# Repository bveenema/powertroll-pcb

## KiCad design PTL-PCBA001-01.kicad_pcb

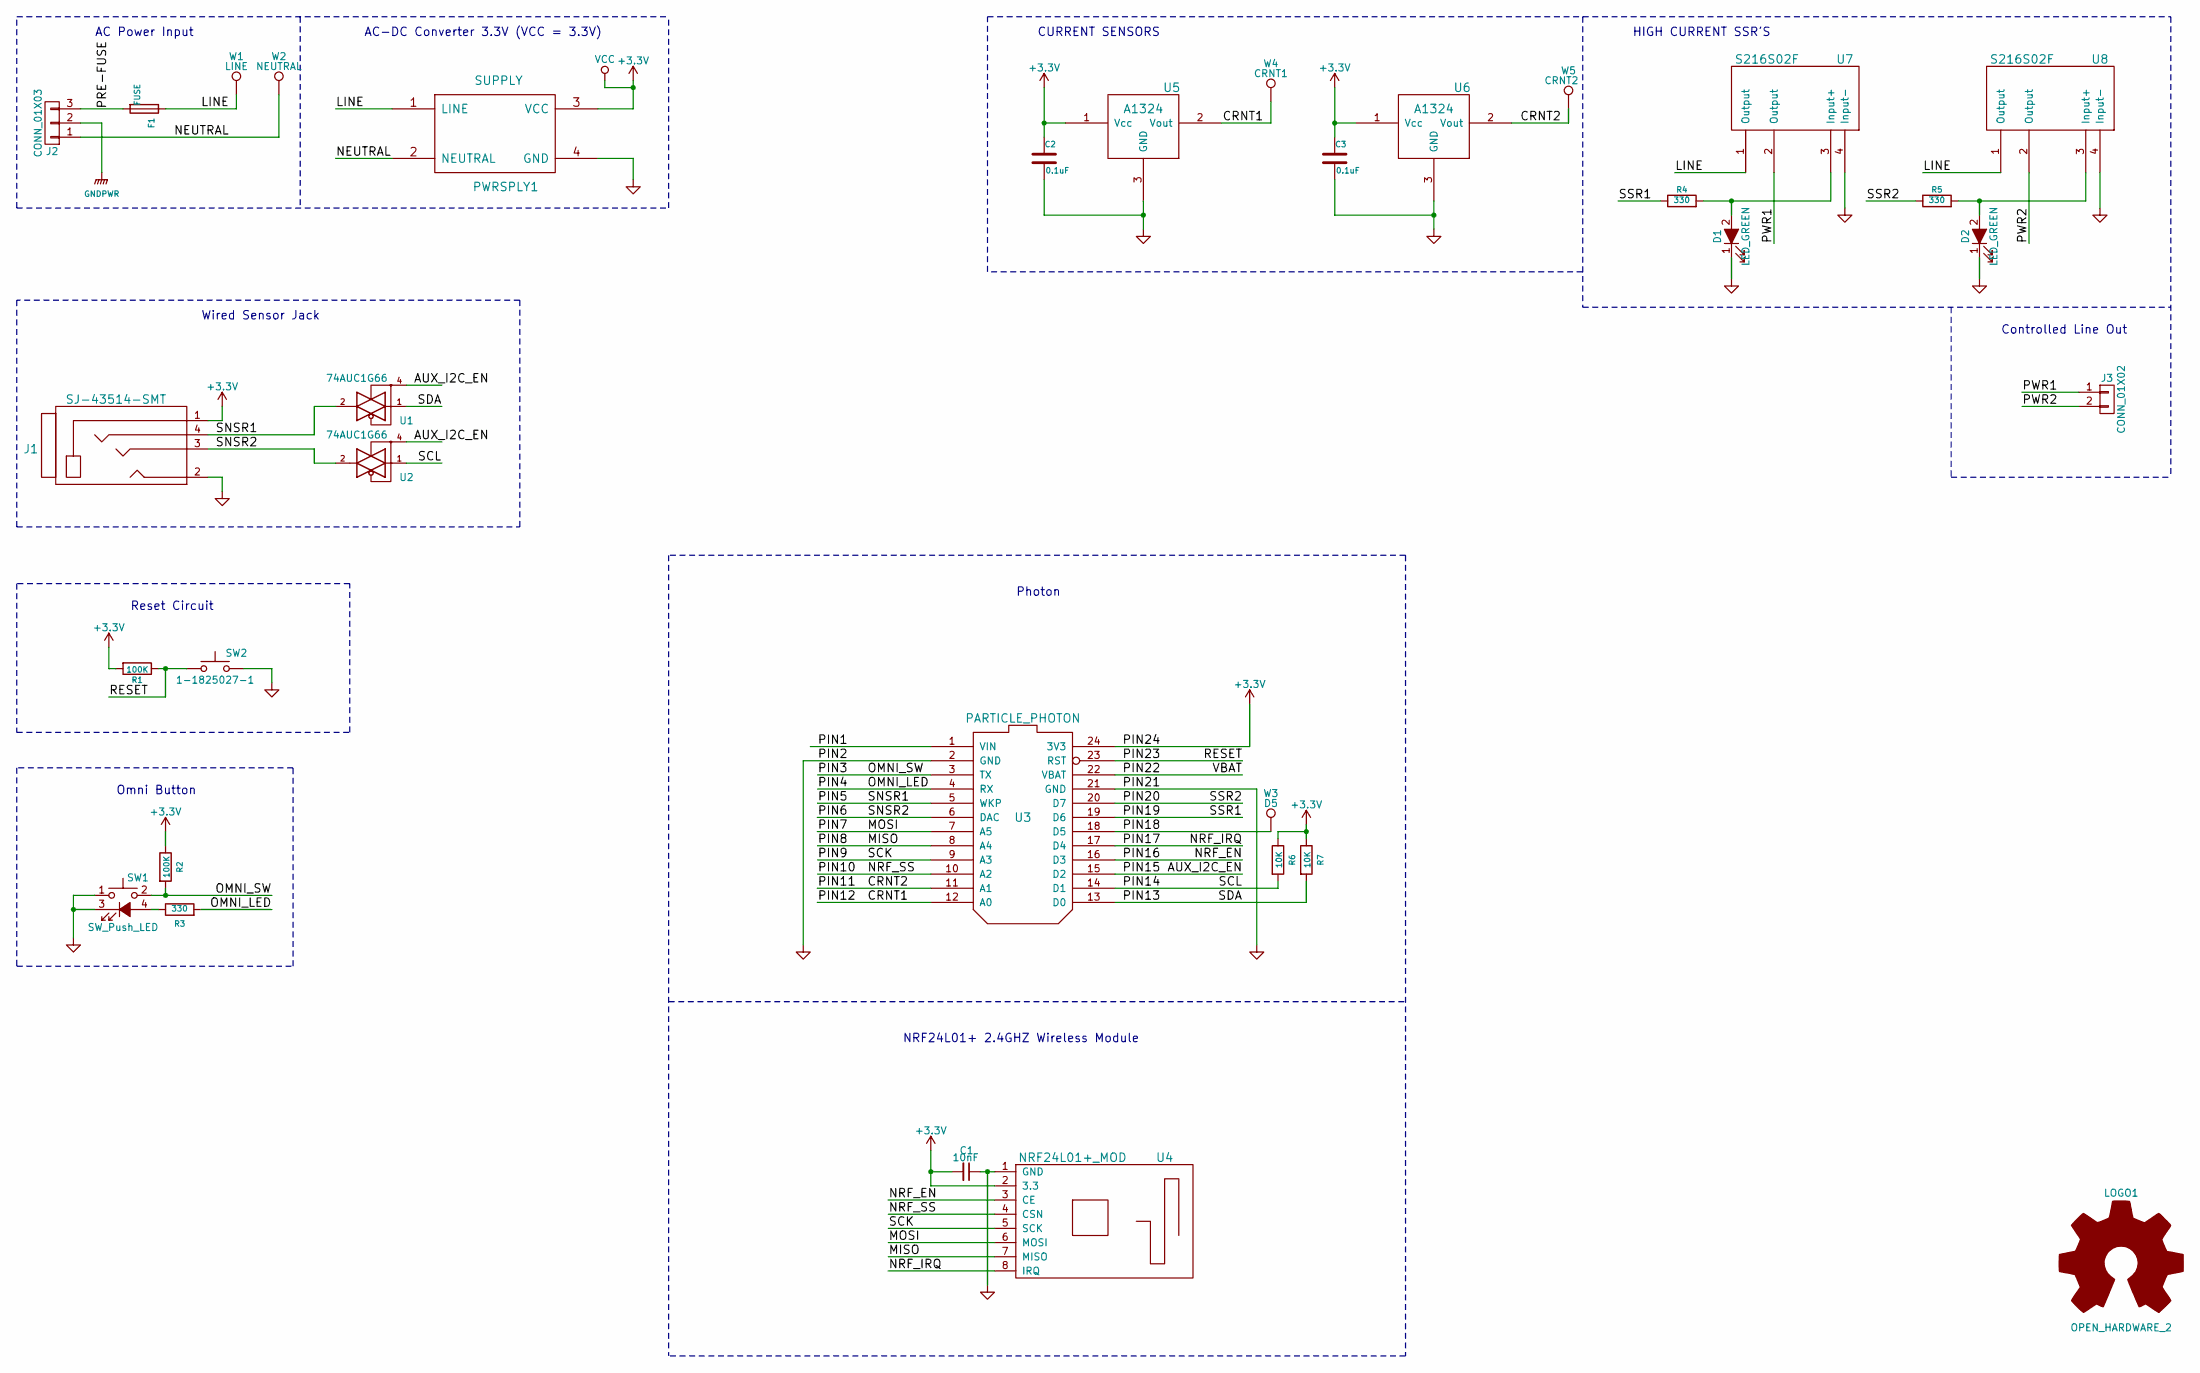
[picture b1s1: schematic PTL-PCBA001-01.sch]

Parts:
C1: 10nF; C_0805; Part Number CL21B103KBANNNC
C2, C3: 0.1uF; C_0805_HandSoldering
D1, D2: LED_GREEN; LED_0805
F1: FUSE; Fuseholder5x20_horiz_open_inline_Type-I
J1: SJ-43514-SMT
J2: CONN_01X03; Molex_UltraFit-1722861103_3x3.50mm_Straight
J3: CONN_01X02; Molex_UltraFit-1722861102_2x3.50mm_Straight
LOGO1: OPEN_HARDWARE_2; OSHW-Symbol_6.7x6mm_SilkScreen
PWRSPLY1: SUPPLY; PowerSupply
R1, R2: 100K; R_0805_HandSoldering
R3, R4, R5: 330; R_0805_HandSoldering
R6, R7: 10K; R_0805_HandSoldering
SW1: SW_Push_LED; JST_PH_B4B-PH-K_04x2.00mm_Straight
SW2: 1-1825027-1; SW_Tactile_SPST_Angled
U1, U2: 74AUC1G66; SOT-23-5
U3: PARTICLE_PHOTON; photon
U4: NRF24L01+_MOD; NRF24L01
U5, U6: A1324; SOT-23
U7, U8: S216S02F; S216S02
W1: LINE; Measurement_Point_Round-TH_Small
W2: NEUTRAL; Measurement_Point_Round-TH_Small
W3: D5; Measurement_Point_Round-TH_Small
W4: CRNT1; Measurement_Point_Round-SMD-Pad_Small
W5: CRNT2; Measurement_Point_Round-SMD-Pad_Small

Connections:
+3V3: C1.2, C2.1, C3.1, J1.1, PWRSPLY1.3 (VCC), R1.2, R2.1, R6.1, R7.1, U1.5 (VCC), U2.5 (VCC), U3.24 (3V3), U4.2 (3.3), U5.1 (Vcc), U6.1 (Vcc)
/AUX_I2C_EN: U1.4, U2.4, U3.15 (D2)
/CRNT1: U3.12 (A0), U5.2 (Vout), W4.1
/CRNT2: U3.11 (A1), U6.2 (Vout), W5.1
/LINE: F1.1, PWRSPLY1.1 (LINE), U7.1 (Output), U8.1 (Output), W1.1
/MISO: U3.8 (A4), U4.7 (MISO)
/MOSI: U3.7 (A5), U4.6 (MOSI)
/NEUTRAL: J2.1, PWRSPLY1.2 (NEUTRAL), W2.1
/NRF_EN: U3.16 (D3), U4.3 (CE)
/NRF_IRQ: U3.17 (D4), U4.8 (IRQ)
/NRF_SS: U3.10 (A2), U4.4 (CSN)
/OMNI_LED: R3.2, U3.4 (RX)
/OMNI_SW: R2.2, SW1.2, U3.3 (TX)
/PIN1: U3.1 (VIN)
/PIN5: J1.4, U1.2, U3.5 (WKP)
/PIN6: J1.3, U2.2, U3.6 (DAC)
/PIN9: U3.9 (A3), U4.5 (SCK)
/PIN13: R7.2, U1.1, U3.13 (D0)
/PIN14: R6.2, U2.1, U3.14 (D1)
/PIN18: U3.18 (D5), W3.1
/PIN19: R4.1, U3.19 (D6)
/PIN20: R5.1, U3.20 (D7)
/PIN22: U3.22 (VBAT)
/PIN23: R1.1, SW2.1, U3.23 (RST)
/PRE-FUSE: F1.2, J2.3
/PWR1: J3.1, U7.2 (Output)
/PWR2: J3.2, U8.2 (Output)
GND: C1.1, C2.2, C3.2, D1.1 (K), D2.1 (K), J1.2, PWRSPLY1.4 (GND), SW1.1, SW1.3 (K), SW2.2, U1.3 (GND), U2.3 (GND), U3.2 (GND), U3.21 (GND), U4.1 (GND), U5.3 (GND), U6.3 (GND), U7.4 (Input-), U8.4 (Input-)
GNDPWR: J2.2
unnamed: D1.2 (A), R4.2, U7.3 (Input+)
unnamed: D2.2 (A), R5.2, U8.3 (Input+)
unnamed: R3.1, SW1.4 (A)

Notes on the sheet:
HIGH CURRENT SSR'S
CURRENT SENSORS
AC-DC Converter 3.3V (VCC = 3.3V)
AC Power Input
Wired Sensor Jack
Controlled Line Out
Reset Circuit
Photon
NRF24L01+ 2.4GHZ Wireless Module
Omni Button

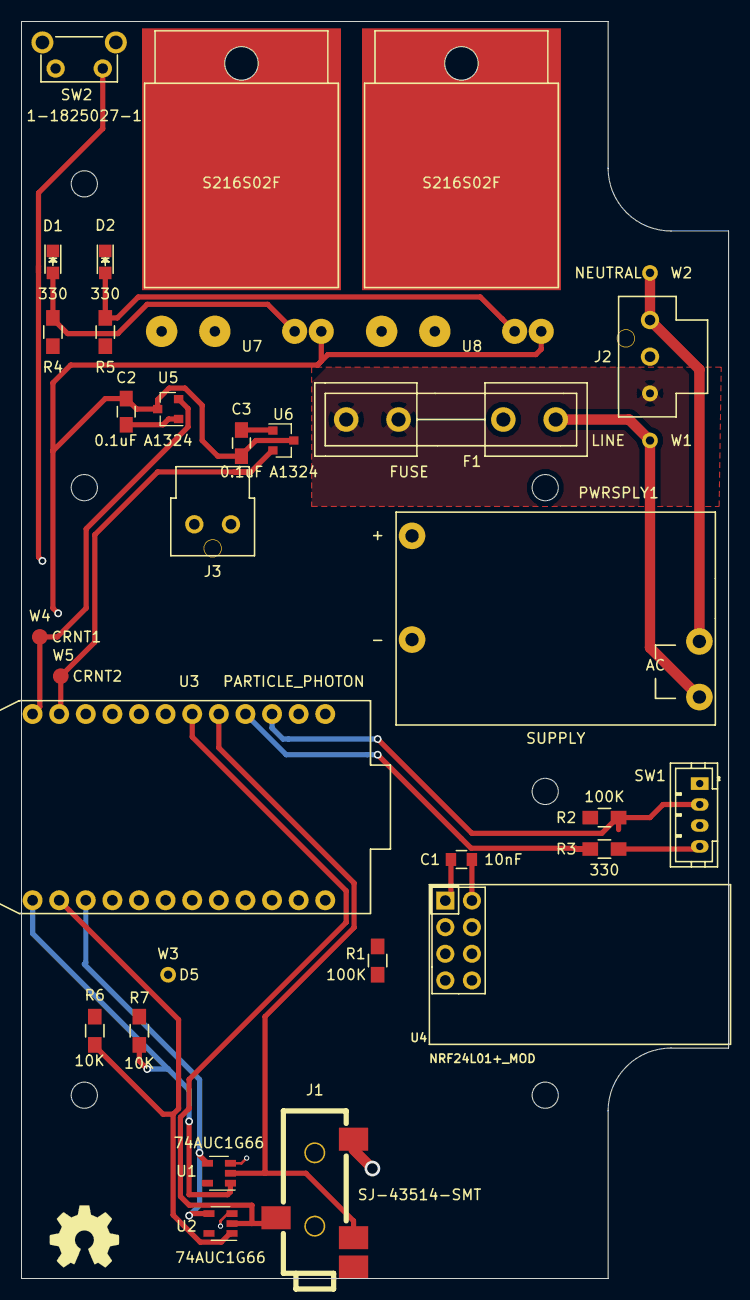
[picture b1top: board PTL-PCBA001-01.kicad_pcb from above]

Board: 2 copper layers, 67.5 x 120.0 mm, 33 parts (0 on the bottom side), 29 nets.

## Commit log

2016-12-19 Included files from previous version
2016-12-20 Completed Schematic
2016-12-21 Restore after Gdrive ruined everything
2017-01-02 Began board layout
2017-01-03 Added ground pours for PWR 1 and PWR 2
    Rearranged a current sensor output and SSR control pins for cleaner
    routing
2017-01-03 Routed OMNI_SW, broke reset trace
2017-01-03 Added ground pour
2017-01-03 Saved project
2017-01-03 Finish rev A design, created gerbers
2017-01-05 Created BOM
2017-01-11 Created PDF Schematic
2017-01-12 Added SPICE simulation of FET Driver
2017-01-12 Updated SPICE model for full sine
2017-01-13 Updated SPICE model
